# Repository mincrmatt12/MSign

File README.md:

# MSign

Code + designs for an LED sign display board powered by an STM32 and ESP8266. Make sure you clone the submodules.

## Organization

- `board`: schematics and PCB layout
- `stm`: STM32 firmware (drives the display)
- `stmboot`: STM32 bootloader
- `esp`: ESP8266 firmware (grabs information from the internet)
- `espweb`: ESP8266 web-based configuration page source
- `cfgserver`: Server for shipping unattended config and software updates (without using the webui)
- `bmap`: Tools for generating graphics resources
- `caplog`: Tools for debugging
- `vendor`: Various dependencies in source form (everything not listed below)
- `sim`: Stubs/shims for running the `esp` and `stm` codebases under linux.

## Dependencies

- A recent `arm-none-eabi-gcc` installation (suitably modern to deal with C++20; GCC 14 is what's tested)
- A `xtensa-lx106-elf-gcc` that can deal with C++20; preferably version 13.2.0 (which was available at one point in debian)
  - A suitable newlib/libstdc++ archive is available in `Dockerfile.build`
- Python 3 and the packages in `requirements.txt`
  - If you aren't building the `espweb` directory you do not require the `cryptography` package listed
- OpenOCD (for flashing)
  - If you have PlatformIO installed we use its OpenOCD by default, so you may not need to install it system-wide.
- CMake (version 3.13 or later is recommended)
- `quilt`, to apply the patches in `vendor` for the ESP8266 SDK

and everything checked out in the `vendor` directory. The ESP8266 SDK also usually requests you have python (specifically _system_ python, whatever runs from `python`) installed with it's requirements (`vendor/ESP8266_RTOS_SDK/requirements.txt`)

A Docker file with these is provided as `Dockerfile.build`.

For building the `espweb` you also need:

- yarn
- node 

A Docker file with _these_ is also provided as `Dockerfile.webbuild`

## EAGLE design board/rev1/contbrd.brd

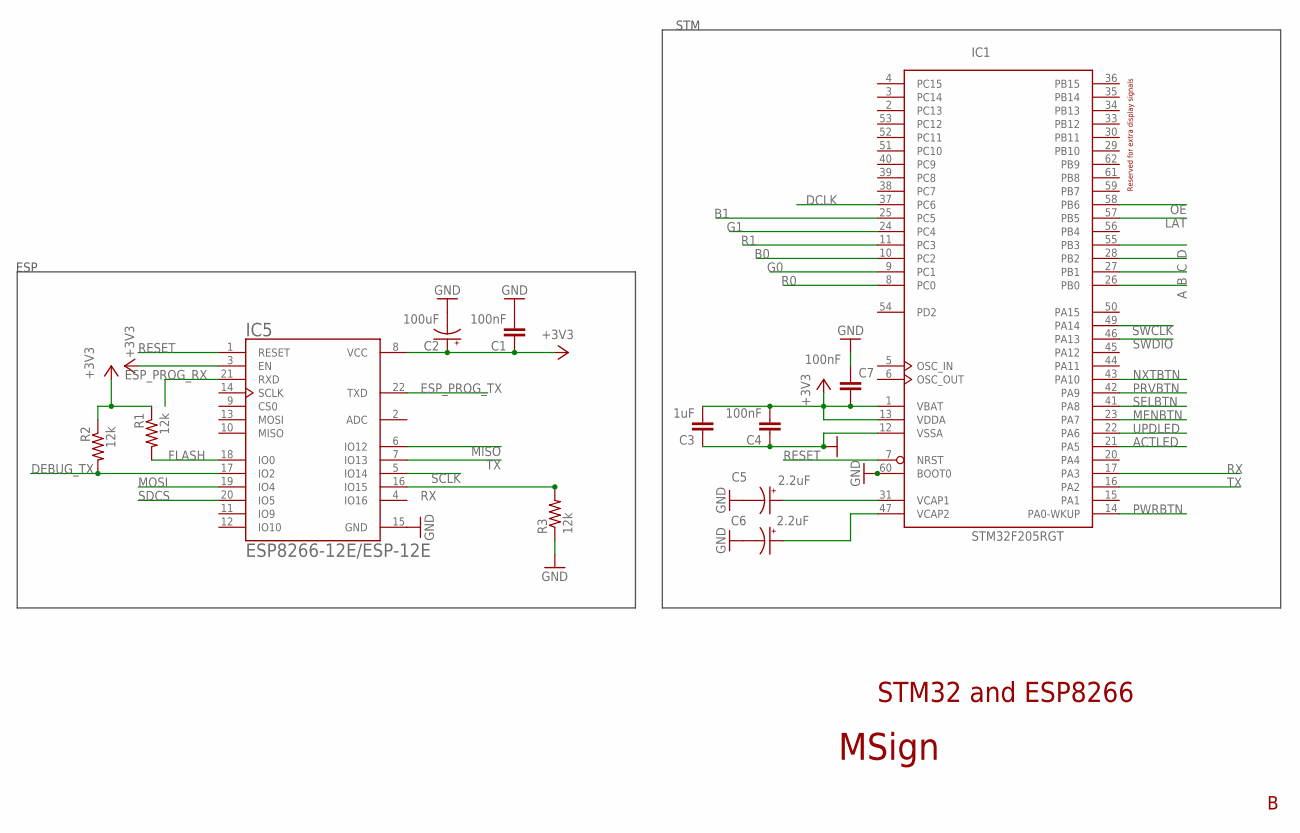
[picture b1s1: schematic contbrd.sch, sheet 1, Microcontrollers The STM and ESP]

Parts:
C1, C4, C7: 100nF; C025-025X050
C2: 100uF; E2,5-6
C3: 1uF; C050-024X044
C5, C6: 2.2uF; E1,8-4
IC1: STM32F205RGT; LQFP64
IC5: ESP8266-12E/ESP-12E; XCVR_ESP8266-12E/ESP-12E
R1, R2, R3: 12k; 0204/7

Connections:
+3V3: C1.1, C2.+, C3.2, C4.2, C7.2, IC1.1 (VBAT), IC1.13 (VDDA), IC5.3 (EN), IC5.8 (VCC), R1.1, R2.1; also elsewhere on the board
A: IC1.26 (PB0); also elsewhere on the board
ACTLED: IC1.21 (PA5); also elsewhere on the board
B: IC1.27 (PB1); also elsewhere on the board
B0: IC1.10 (PC2); also elsewhere on the board
B1: IC1.25 (PC5); also elsewhere on the board
C: IC1.28 (PB2); also elsewhere on the board
D: IC1.55 (PB3); also elsewhere on the board
DCLK: IC1.37 (PC6); also elsewhere on the board
DEBUG_TX: IC5.17 (IO2), R2.2; also elsewhere on the board
ESP_PROG_RX: IC5.21 (RXD); also elsewhere on the board
ESP_PROG_TX: IC5.22 (TXD); also elsewhere on the board
FLASH: IC5.18 (IO0), R1.2; also elsewhere on the board
G0: IC1.9 (PC1); also elsewhere on the board
G1: IC1.24 (PC4); also elsewhere on the board
GND: C1.2, C2.-, C3.1, C4.1, C5.-, C6.-, C7.1, IC1.12 (VSSA), IC1.60 (BOOT0), IC5.15 (GND), R3.1; also elsewhere on the board
LAT: IC1.57 (PB5); also elsewhere on the board
MENBTN: IC1.23 (PA7); also elsewhere on the board
MISO: IC5.6 (IO12); also elsewhere on the board
MOSI: IC5.19 (IO4); also elsewhere on the board
unnamed: C5.+, IC1.31 (VCAP1)
unnamed: C6.+, IC1.47 (VCAP2)
NXTBTN: IC1.43 (PA10); also elsewhere on the board
OE: IC1.58 (PB6); also elsewhere on the board
PRVBTN: IC1.42 (PA9); also elsewhere on the board
PWRBTN: IC1.14 (PA0-WKUP); also elsewhere on the board
R0: IC1.8 (PC0); also elsewhere on the board
R1: IC1.11 (PC3); also elsewhere on the board
RESET: IC1.7 (NRST), IC5.1 (RESET); also elsewhere on the board
RX: IC1.17 (PA3), IC5.16 (IO15), R3.2
SCLK: IC5.5 (IO14); also elsewhere on the board
SDCS: IC5.20 (IO5); also elsewhere on the board
SELBTN: IC1.41 (PA8); also elsewhere on the board
SWCLK: IC1.49 (PA14); also elsewhere on the board
SWDIO: IC1.46 (PA13); also elsewhere on the board
TX: IC1.16 (PA2), IC5.7 (IO13)
UPDLED: IC1.22 (PA6); also elsewhere on the board

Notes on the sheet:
ESP
STM
MSign
STM32 and ESP8266
Reserved for extra display signals

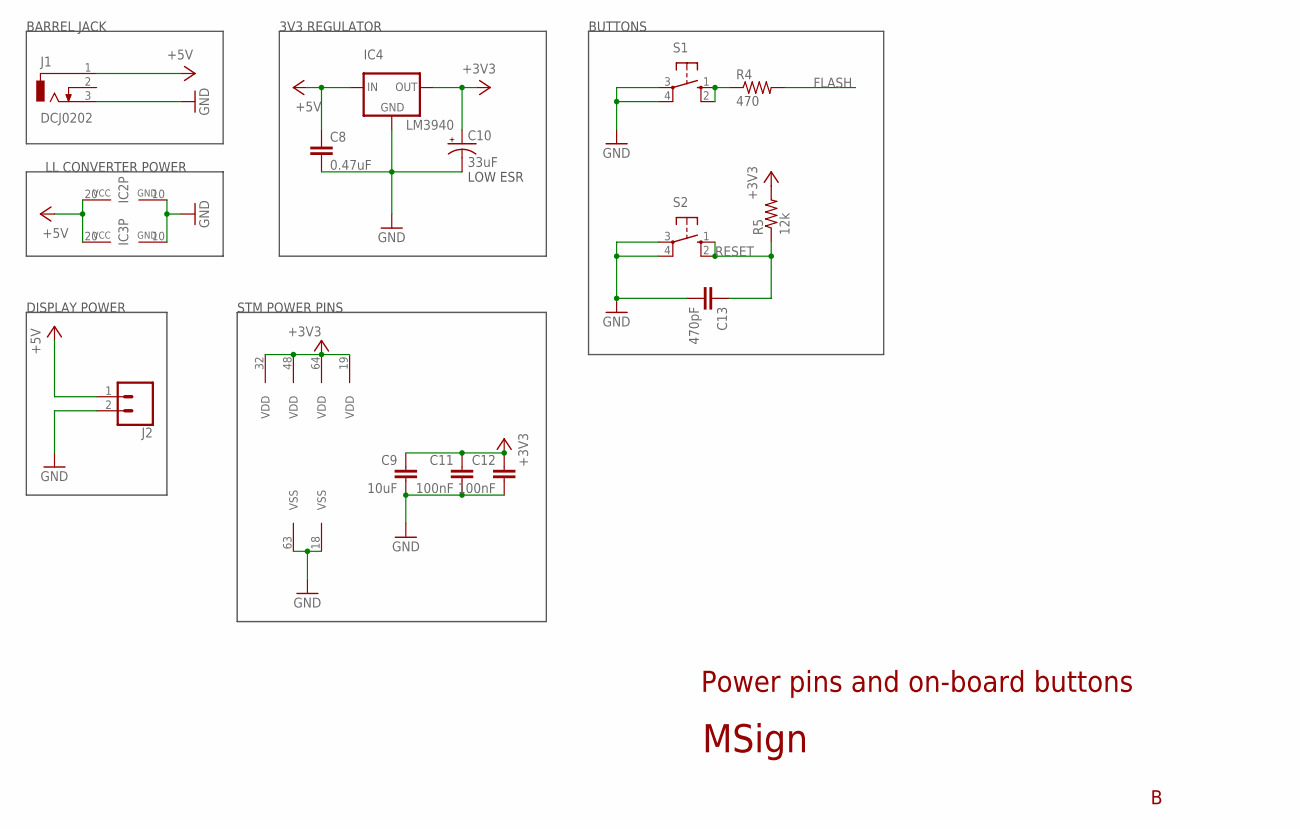
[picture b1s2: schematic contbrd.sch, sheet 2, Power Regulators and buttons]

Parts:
C8: 0.47uF; C050-024X044
C9: 10uF; C025-025X050
C10: 33uF; E2-5
C11, C12: 100nF; C025-025X050
C13: 470pF; C025-025X050
IC1: STM32F205RGT; LQFP64
IC2, IC3: 74HCT244DW; SO20W
IC4: LM3940; TO220
J1: DCJ0202
J2: CONN_025MM; SCREWTERMINAL-5MM-2
R4: 470; 0204/7
R5: 12k; 0204/7
S1, S2: 10-XX; B3F-10XX

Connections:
+3V3: C9.1, C10.+, C11.1, C12.1, IC1.19 (VDD), IC1.32 (VDD), IC1.48 (VDD), IC1.64 (VDD), IC4.3 (OUT), R5.2; also elsewhere on the board
+5V: C8.1, IC2.20 (VCC), IC3.20 (VCC), IC4.1 (IN), J1.1, J2.1
FLASH: R4.2; also elsewhere on the board
GND: C8.2, C9.2, C10.-, C11.2, C12.2, C13.2, IC1.18 (VSS), IC1.63 (VSS), IC2.10 (GND), IC3.10 (GND), IC4.2 (GND), J1.3, J2.2, S1.3, S1.4 (P1), S2.3, S2.4 (P1); also elsewhere on the board
unnamed: R4.1, S1.1 (S), S1.2 (S1)
RESET: C13.1, R5.1, S2.1 (S), S2.2 (S1); also elsewhere on the board

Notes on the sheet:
DISPLAY POWER
BARREL JACK
LOW ESR
STM POWER PINS
3V3 REGULATOR
BUTTONS
LL CONVERTER POWER
MSign
Power pins and on-board buttons

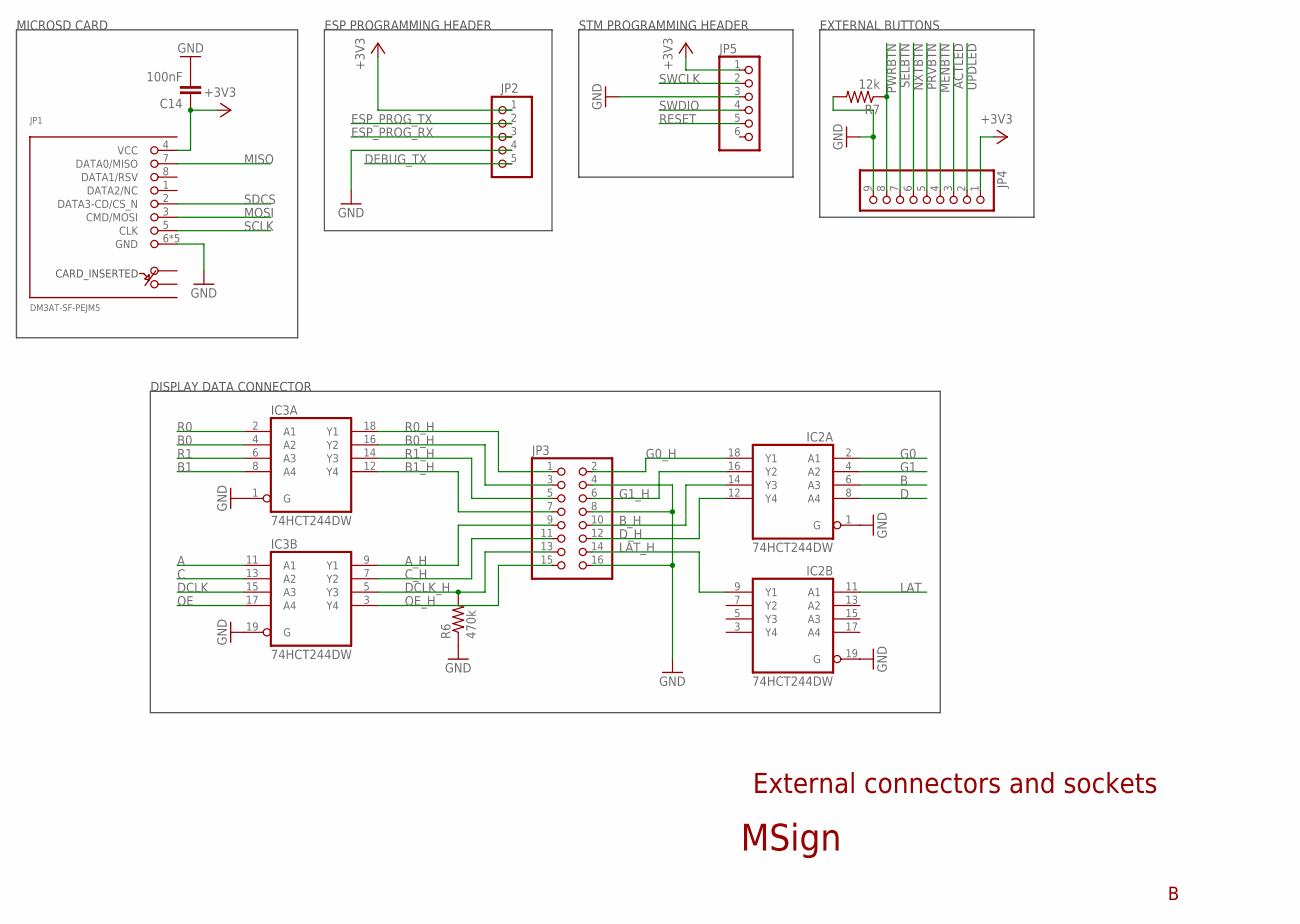
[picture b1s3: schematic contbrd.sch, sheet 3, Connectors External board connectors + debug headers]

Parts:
C14: 100nF; C025-025X050
IC2, IC3: 74HCT244DW; SO20W
JP1: DM3AT-SF-PEJM5
JP2: PINHD-1X5; 1X05
JP3: PINHD-2X8; 2X08
JP4: PINHD-1X9; 1X09
JP5: PINHD-1X6; 1X06
R6: 470k; 0204/7
R7: 12k; 0204/7

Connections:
+3V3: C14.1, JP1.4 (VCC), JP2.1, JP4.1, JP5.1; also elsewhere on the board
A: IC3.11 (A1); also elsewhere on the board
ACTLED: JP4.3; also elsewhere on the board
A_H: IC3.9 (Y1), JP3.9
B: IC2.6 (A3); also elsewhere on the board
B0: IC3.4 (A2); also elsewhere on the board
B0_H: IC3.16 (Y2), JP3.3
B1: IC3.8 (A4); also elsewhere on the board
B1_H: IC3.12 (Y4), JP3.7
B_H: IC2.14 (Y3), JP3.10
C: IC3.13 (A2); also elsewhere on the board
C_H: IC3.7 (Y2), JP3.11
D: IC2.8 (A4); also elsewhere on the board
DCLK: IC3.15 (A3); also elsewhere on the board
DCLK_H: IC3.5 (Y3), JP3.13, R6.2
DEBUG_TX: JP2.5; also elsewhere on the board
D_H: IC2.12 (Y4), JP3.12
ESP_PROG_RX: JP2.3; also elsewhere on the board
ESP_PROG_TX: JP2.2; also elsewhere on the board
G0: IC2.2 (A1); also elsewhere on the board
G0_H: IC2.18 (Y1), JP3.2
G1: IC2.4 (A2); also elsewhere on the board
G1_H: IC2.16 (Y2), JP3.6
GND: C14.2, IC2.1 (G), IC2.19 (G), IC3.1 (G), IC3.19 (G), JP1.6 (GND), JP1.MOUNT0 (GND), JP1.MOUNT1 (GND), JP1.MOUNT2 (GND), JP1.MOUNT3 (GND), JP2.4, JP3.4, JP3.8, JP3.16, JP4.9, JP5.3, R6.1, R7.2; also elsewhere on the board
LAT: IC2.11 (A1); also elsewhere on the board
LAT_H: IC2.9 (Y1), JP3.14
MENBTN: JP4.4; also elsewhere on the board
MISO: JP1.7 (DATA0/MISO); also elsewhere on the board
MOSI: JP1.3 (CMD/MOSI); also elsewhere on the board
NXTBTN: JP4.6; also elsewhere on the board
OE: IC3.17 (A4); also elsewhere on the board
OE_H: IC3.3 (Y4), JP3.15
PRVBTN: JP4.5; also elsewhere on the board
PWRBTN: JP4.8, R7.1; also elsewhere on the board
R0: IC3.2 (A1); also elsewhere on the board
R0_H: IC3.18 (Y1), JP3.1
R1: IC3.6 (A3); also elsewhere on the board
R1_H: IC3.14 (Y3), JP3.5
RESET: JP5.5; also elsewhere on the board
SCLK: JP1.5 (CLK); also elsewhere on the board
SDCS: JP1.2 (DATA3-CD/CS_N); also elsewhere on the board
SELBTN: JP4.7; also elsewhere on the board
SWCLK: JP5.2; also elsewhere on the board
SWDIO: JP5.4; also elsewhere on the board
UPDLED: JP4.2; also elsewhere on the board

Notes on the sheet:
DISPLAY DATA CONNECTOR
MICROSD CARD
ESP PROGRAMMING HEADER
STM PROGRAMMING HEADER
MSign
External connectors and sockets
EXTERNAL BUTTONS

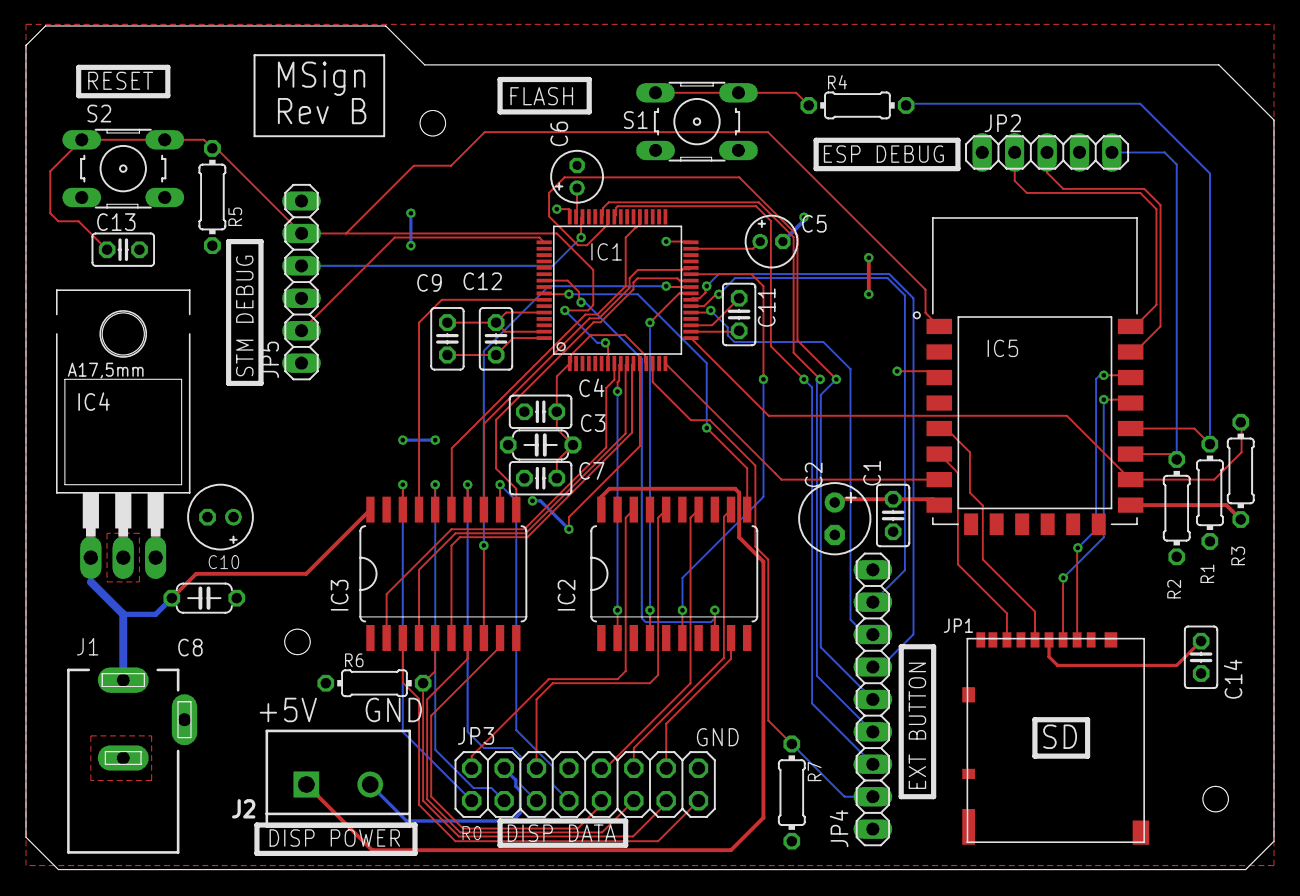
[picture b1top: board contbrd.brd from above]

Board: 2 copper layers, 97.8 x 66.1 mm, 35 parts (0 on the bottom side), 52 nets.

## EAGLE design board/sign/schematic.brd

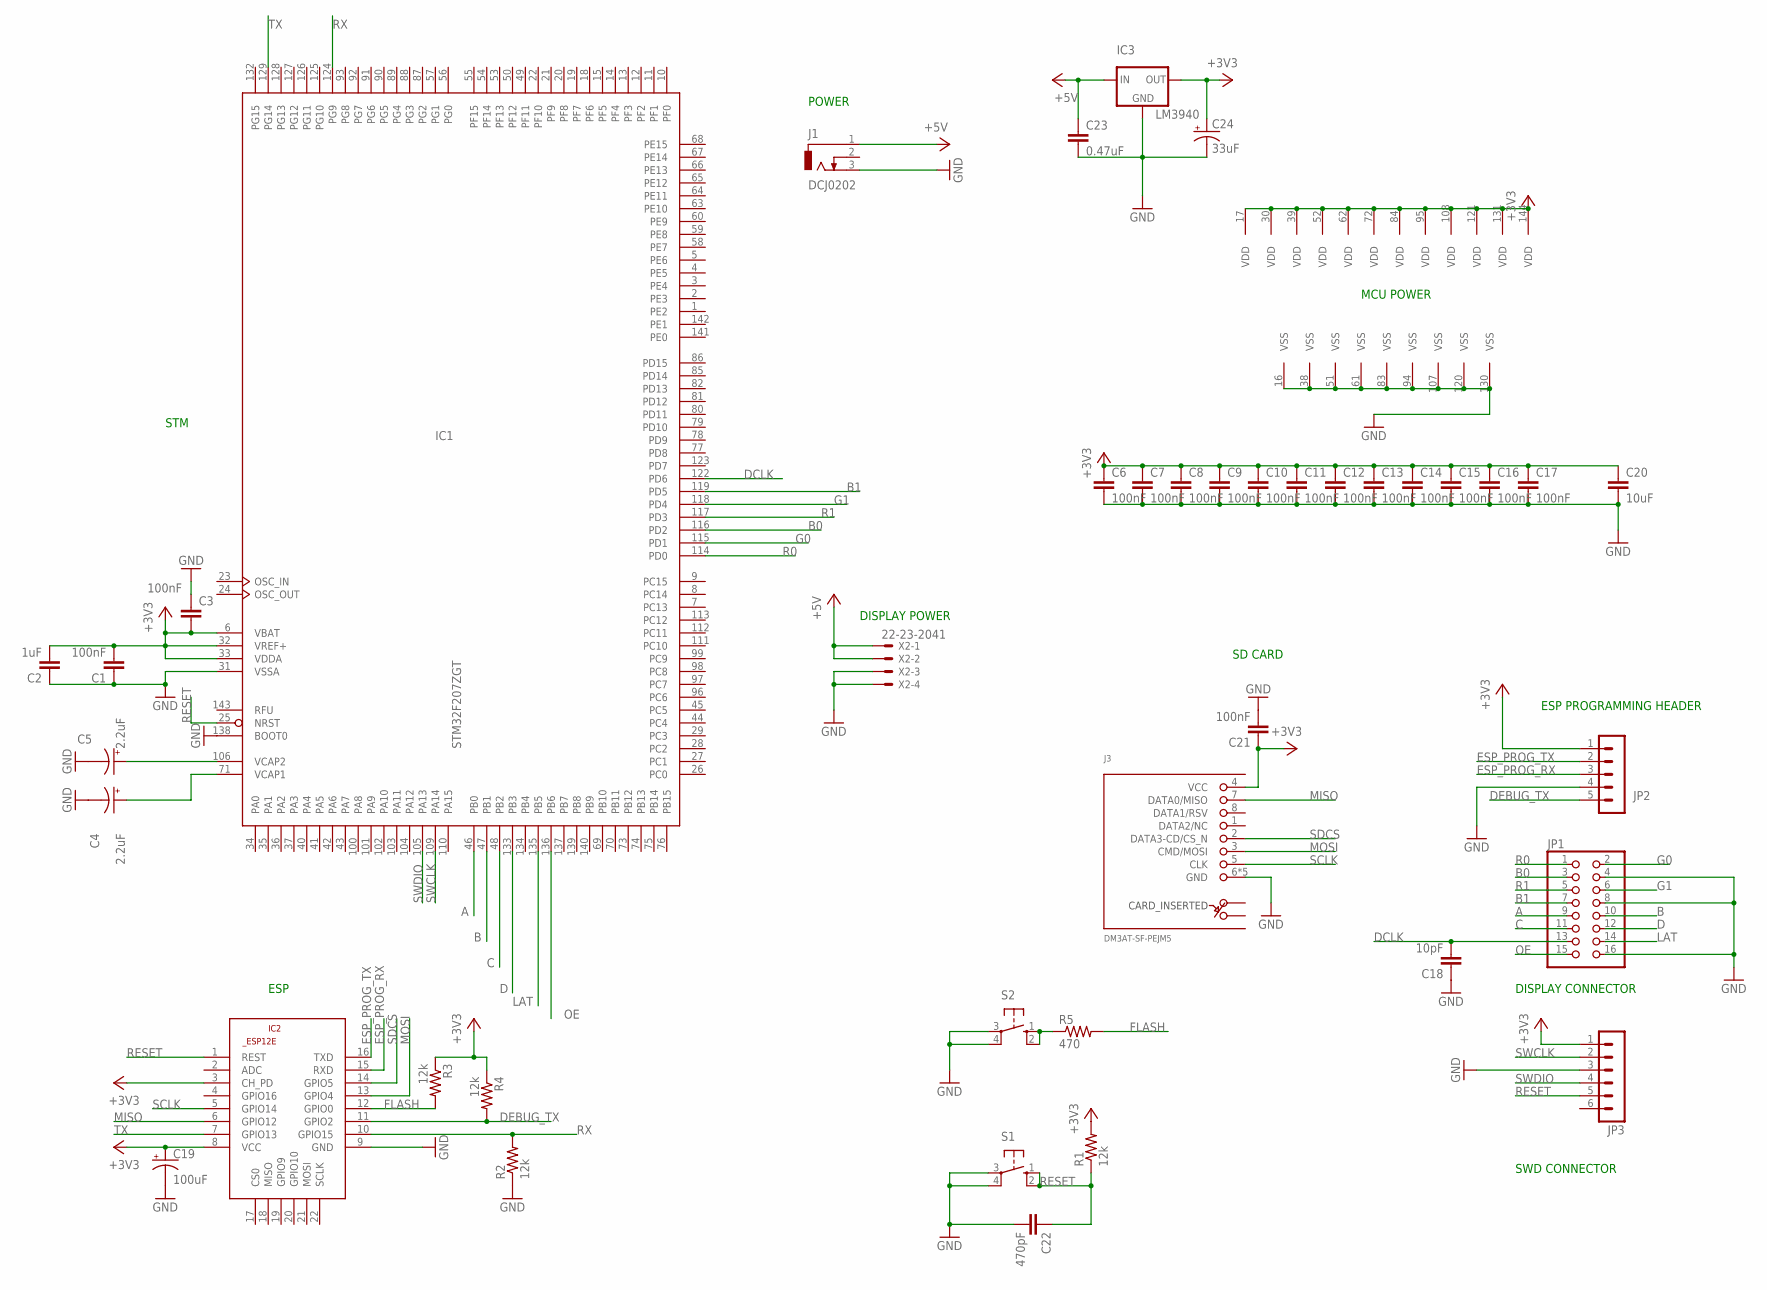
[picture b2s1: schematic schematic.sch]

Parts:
C1, C3, C6, C7, C8, C9, C10, C11, C12, C13, C14, C15, C16, C17, C21: 100nF; C025-025X050
C2: 1uF; C050-024X044
C4, C5: 2.2uF; E1,8-4
C18: 10pF; C050-024X044
C19: 100uF; E2,5-6
C20: 10uF; C025-025X050
C22: 470pF; C025-025X050
C23: 0.47uF; C050-024X044
C24: 33uF; E2-5
IC1: STM32F207ZGT; LQFP144
IC2: ESP8266-12EESP12E; ESP8266-ESP12E
IC3: LM3940; TO220
J1: DCJ0202
J3: DM3AT-SF-PEJM5
JP1: PINHD-2X8; 2X08
JP2: MA05-1
JP3: MA06-1
R1, R2, R3, R4: 12k; 0204/7
R5: 470; 0204/7
S1, S2: 10-XX; B3F-10XX
X2: 22-23-2041

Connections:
+3V3: C1.2, C2.2, C3.2, C6.1, C7.1, C8.1, C9.1, C10.1, C11.1, C12.1, C13.1, C14.1, C15.1, C16.1, C17.1, C19.+, C20.1, C21.1, C24.+, IC1.6 (VBAT), IC1.17 (VDD), IC1.30 (VDD), IC1.32 (VREF+), IC1.33 (VDDA), IC1.39 (VDD), IC1.52 (VDD), IC1.62 (VDD), IC1.72 (VDD), IC1.84 (VDD), IC1.95 (VDD), IC1.108 (VDD), IC1.121 (VDD), IC1.131 (VDD), IC1.144 (VDD), IC2.3 (CH_PD), IC2.8 (VCC), IC3.3 (OUT), J3.4 (VCC), JP2.1, JP3.1, R1.2, R3.1, R4.1
+5V: C23.1, IC3.1 (IN), J1.1, X2.1, X2.2
A: IC1.46 (PB0), JP1.9
B: IC1.47 (PB1), JP1.10
B0: IC1.116 (PD2), JP1.3
B1: IC1.119 (PD5), JP1.7
C: IC1.48 (PB2), JP1.11
D: IC1.133 (PB3), JP1.12
DCLK: C18.2, IC1.122 (PD6), JP1.13
DEBUG_TX: IC2.11 (GPIO2), JP2.5, R4.2
ESP_PROG_RX: IC2.15 (RXD), JP2.3
ESP_PROG_TX: IC2.16 (TXD), JP2.2
FLASH: IC2.12 (GPIO0), R3.2, R5.2
G0: IC1.115 (PD1), JP1.2
G1: IC1.118 (PD4), JP1.6
GND: C1.1, C2.1, C3.1, C4.-, C5.-, C6.2, C7.2, C8.2, C9.2, C10.2, C11.2, C12.2, C13.2, C14.2, C15.2, C16.2, C17.2, C18.1, C19.-, C20.2, C21.2, C22.2, C23.2, C24.-, IC1.16 (VSS), IC1.31 (VSSA), IC1.38 (VSS), IC1.51 (VSS), IC1.61 (VSS), IC1.83 (VSS), IC1.94 (VSS), IC1.107 (VSS), IC1.120 (VSS), IC1.130 (VSS), IC1.138 (BOOT0), IC2.9 (GND), IC3.2 (GND), J1.3, J3.6 (GND), J3.MOUNT0 (GND), J3.MOUNT1 (GND), J3.MOUNT2 (GND), J3.MOUNT3 (GND), JP1.4, JP1.8, JP1.16, JP2.4, JP3.3, R2.1, S1.3, S1.4 (P1), S2.3, S2.4 (P1), X2.3, X2.4
LAT: IC1.135 (PB5), JP1.14
MISO: IC2.6 (GPIO12), J3.7 (DATA0/MISO)
MOSI: IC2.13 (GPIO4), J3.3 (CMD/MOSI)
unnamed: R5.1, S2.1 (S), S2.2 (S1)
unnamed: C5.+, IC1.106 (VCAP2)
unnamed: C4.+, IC1.71 (VCAP1)
OE: IC1.136 (PB6), JP1.15
R0: IC1.114 (PD0), JP1.1
R1: IC1.117 (PD3), JP1.5
RESET: C22.1, IC1.25 (NRST), IC2.1 (REST), JP3.5, R1.1, S1.1 (S), S1.2 (S1)
RX: IC1.124 (PG9), IC2.10 (GPIO15), R2.2
SCLK: IC2.5 (GPIO14), J3.5 (CLK)
SDCS: IC2.14 (GPIO5), J3.2 (DATA3-CD/CS_N)
SWCLK: IC1.109 (PA14), JP3.2
SWDIO: IC1.105 (PA13), JP3.4
TX: IC1.129 (PG14), IC2.7 (GPIO13)

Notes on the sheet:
MCU POWER
DISPLAY POWER
POWER
SD CARD
ESP
STM
DISPLAY CONNECTOR
ESP PROGRAMMING HEADER
SWD CONNECTOR

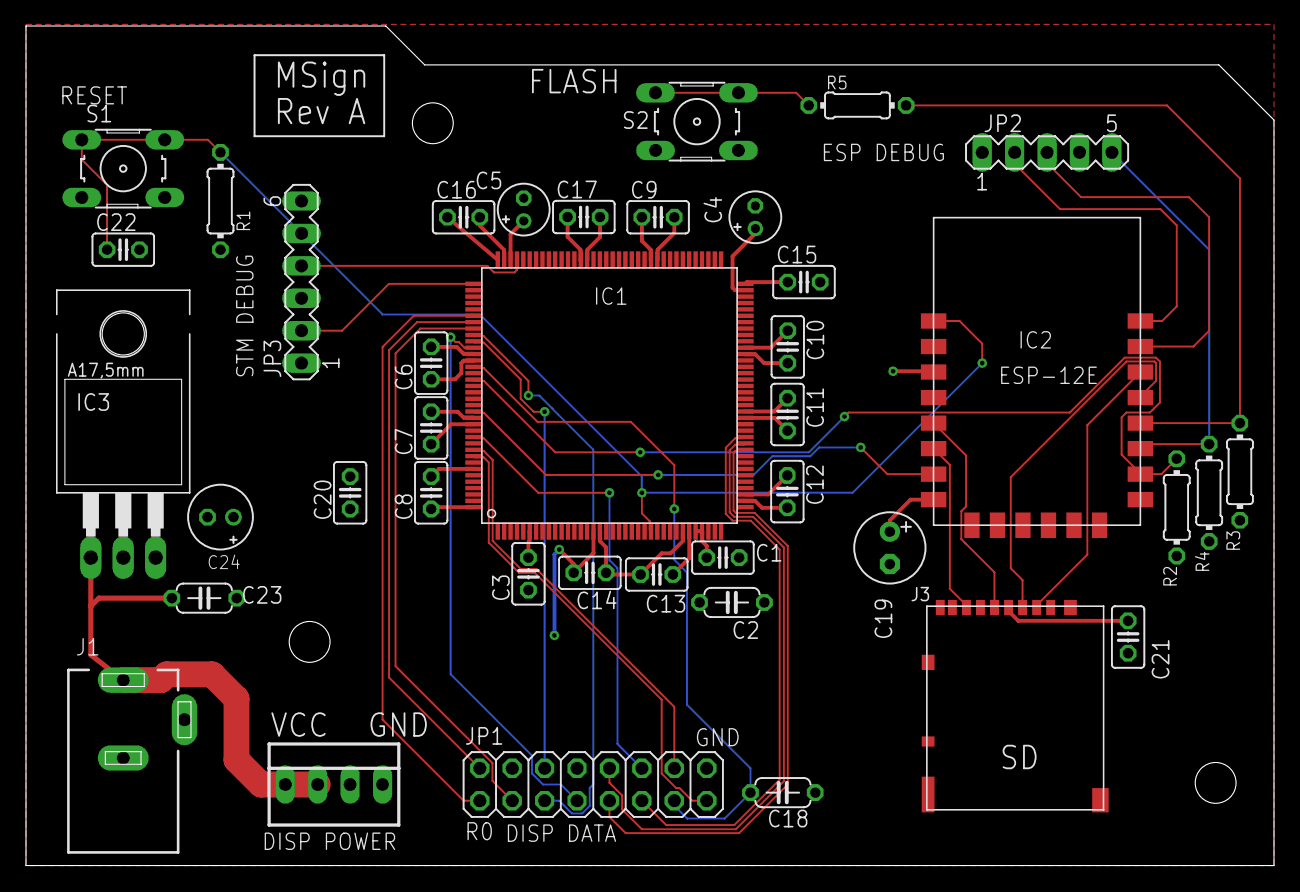
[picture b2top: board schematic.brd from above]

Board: 2 copper layers, 97.8 x 65.8 mm, 40 parts (0 on the bottom side), 32 nets.

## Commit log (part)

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2023-12-26 Add script to unpack a json dump with slotlib prettyprinting
2023-12-26 Sync octoprint on 409 case because update_slot() was going the nocopy route
2023-12-27 Add more outline text overloads
2023-12-27 Remove geocoding
2023-12-27 Fix template deduction on GCC 12
2023-12-27 Reopen file
2023-12-27 More sd error checking pt the third
    this time for writes not reads!
2023-12-27 Hide filename when no print job is loaded
2023-12-28 Fix octoprint grabber completion
    (from 0-100, not 0-1)
2023-12-28 Add printer icon animation
2023-12-28 Add new octoprint options to webui
2023-12-28 Scale bitmaps to dim - 1 instead of dim
    we want the pixels to occupy coordinates from [0, dim), so we
    need to multiply the 0.0-1.0 coords by dim - 1, not dim
2023-12-30 Adjust dupm queue timeout to 0 for requests from serial
    This prevents a deadlock of the form:
    - dupm queue fills
    - dupm waits for packet
    - serial gets a DATA_TEMP message
    - serial waits for 5 seconds for empty space in dupm
    - dupm wait timeout expires
2023-12-31 Implement analog stick
2023-12-31 Use up as virtual previous, not down
2023-12-31 Swap ADC pins with TAB/SEL buttons
    their original pins are not adc inputs. rev2 board will fix this if
    I ever manufacture it
2023-12-31 Ignore kicad lock files in board/
2023-12-31 Add joystick interaction to octoprint screen
    also speed up rendering hopefully with faster rounding
2023-12-31 Fix duplicated scroll table entry
2024-01-01 Add more fs validation in the octoprint bitmap handler
2024-01-01 Ensure restarting HTTP reconnects to try to avoid octoprint kicking us for being slow
2024-01-02 Use midnight as end of day for parcel est. delivery
2024-01-04 Document required fields
2024-01-04 Quantize times to <5minutes where applicable.
2024-01-05 Limit minutely data
2024-01-06 Add serial::interface.update_slot_at_inline
2024-01-06 Fix infinite loop in precip graph draw
2024-01-06 Resolve all interrupt handlers in log to names
2024-01-06 Ensure stm_crash target gets -O2 at least
2024-01-06 Fix missing sync after appending to summary buffer
    also wrong length calc
2024-01-06 Be less conservative in deeming precipitation "unlikely"
2024-01-06 Send grab task high watermark in metrics reports
2024-01-07 Adjust wording for "tomorrow night" when referring to next morning
2024-01-07 Fix rounding issues in bheap
    Problems resulting from the previous fix (now instead of bheap
    corruption, we had bheap infinite loops!)
2024-01-07 Remove erroneous public: in bheap method
    (was added for testing, forgot to remove)
2024-01-07 Add vendor/ to rgignore
2024-01-08 Fix missing "and" in summarizer
2024-01-09 Adjust interaction speeds in weather graph
2024-01-10 Adjust windy icon threshold
2024-01-10 Fix weathersummarizer fusing of unbounded minutely blocks
2024-01-12 Fix cfgserver typos
2024-01-12 Bump cfgserver to 0.1.5
2024-01-25 Ensure cache dir exists in yarn container
2024-02-03 Fix wtest argc check
2024-02-09 Ensure fused data does not limit precision in summaries
2024-02-13 Fix broken check for previous amt in summarizer
2024-02-13 Remove max_hourly_precision in favour of per-timespec precision
2024-03-11 Begin five-day forecast view
2024-03-11 Add five-day forecast view
2024-03-11 Fix arrows in fiveday view
2024-03-18 Add ESP8266 panic/crashlog saving
    After a fatal error, we write the crashlog contents (or at least
    the backtrace; the other PANIC() messages aren't captured at the moment)
    into RAM, then on the next boot we write that message to the SD card.
2024-03-18 Ensure no null bytes wind up in crash log files
2024-03-23 Ensure STM does not freeze after ESP crash during sleep
2024-04-19 Fix detection of likely/unlikely precipitation
2024-04-23 Use a heap-allocated larger file send buffer where possible
2024-06-07 Put minimum bound on precipitation probability when the icon is set
    This avoids a lot of the "rain starting in <5 minutes" summaries that
    go on perpetually despite the server-side icon assignments making
    physical sense.
2024-06-08 Halfhearted attempt to deal with hour 0 offset in minutes
    really should be plumbed through as_minutes()
2024-06-15 Add translate_messages to espweb
2024-06-16 Fix should_ignore_hourly_summary
2024-06-18 Revert broken fix in weathersummarizer
2024-06-24 Show parcel status when only icon is available
2024-06-24 Fix condition in parcels
2024-06-24 Fix alignment
2024-06-28 Remove unused class icons
    (used to be in tdsb grabber, no longer used)
2024-06-29 Store snow depth instead of speed on daily precip
2024-06-29 Add raw_timestamp to espweb
2024-07-03 Refactor parcel status matching
2024-07-03 Fix buggy weather data fuse
    Still obviously not considering the actual hour offset but meh.
2024-07-08 Remove unused vera_8 font
2024-07-10 Limit range on hourly precipitation to preserve precision
2024-07-11 Fix parcel long scroll flicker
2024-07-13 update buttons kicad project files after kicad 8
    some extra fields get generated... who knows?
2024-07-13 Remove libc dependency from stmboot
    Also doesn't link against libgcc, which is technically wrong but the
    bootloader is not meant to use any of the things libgcc fills anyways.
2024-07-14 Remove stm dependency on newlib
    The entirety of the stm codebase right now only relied on:
    - mem{move,cpy,set}: trivial to reimplement (even without
    optimizations, just using -O3 on a naive implementation generates
    suitable unrolling)
    - strlen & strncpy: also trivial to implement
    - strftime & gmtime_r: replaced with c++ quasi-time.h implementation
2024-07-14 Fix stm build scripts always regenerating stm.bin
2024-07-15 Fix out-of-bounds write in dupm
2024-07-15 Update ESP toolchain
    ARM: 13.3 -> (unchanged)
    ESP: 8.4.0 -> 13.2 (built from 8.4.0 newlib, 13.2 esp32 libstdc++ and debian GCC)
    Debian: bookworm -> trixie
2024-07-15 Fix dockerfile to work from an unpatched SDK
2024-07-22 Allow wildcard dirtag matches in ttc
2024-08-09 Add degree symbol to tahoma_9 font
2024-08-09 Enhance descriptions of weather graphs
    also using the new ° symbol in the font
2024-09-01 Add entry to clangd to remove charset override
    clang doesn't seem to like `cp1252` as a charset
2024-09-01 Adjust gamma from 2.6 to 2.45
    as an experiment
2024-09-07 Minor tweak in locking around slots::TTC_INFO
2024-10-01 Adjust colors on weather for fog
2024-10-01 Fix bug with e-notation in json parser
2024-10-01 Check for memory alloc fail in bearssl_supplicant
2024-10-01 Move lwip clone from savannah.nongnu to the github mirror
2024-10-11 Set wifi free heap threshold to 10k
2024-10-22 Try to re-init wifi after disconnect fail
2024-10-28 Upgrade js dependencies to appease dependabot
2024-10-28 actually call esp_wifi_connect in the reset code
2024-10-30 Fix weather graph occasionally showing negative wind
2024-11-10 Add fix for memory leak in sdk code
    When reconnecting to a WPA2-Enterprise network, the system can decide
    to cache on a reconnection attempt, in which case the EAP sm is not
    cleaned up and roughly 7k is leaked (well, it's referenced by a global
    so will not accumulate over multiple attempts, but still) as a result.
    This adds a few hacks to ensure the SDK code is told about key
    negotiation succeeding regardless - this is complicated by the fact that
2024-11-11 Cleanup TypedBlock helpers and add array size()
    uses requires to conditionally include methods instead of static
    asserts, far cleaner
    also adds a size() to return the array size of a pointer specialization
2024-11-20 Fix snow icon
2024-11-20 Discard GTFS updates if they are empty
    (using old information)
2024-11-20 Add clangd file for stm common
    fixes autocomplete by assuming a boring normal c++20 setup
    for the files which are completely standalone
2024-11-26 Avoid showing 0mm of snow if no accumulation, show rate instead
2024-11-27 Ensure enums with "negative" values get parsed by slotlib
2024-12-10 Add bitmask_of to slots.h
    and support in slotlib - used to mark bitmasks without using enum names
    (works better for multiple fields with same bitmask, like in new sccfg
    status reports)
2025-01-14 Set confgen to parse as c++20
2025-01-14 Fix incomplete refactor on sccfg
2025-01-18 Replace line_impl_low/high with a template
    (and also remove the redundant dx < 0/dy < 0 checks as we
    already swap the points natively)
2025-01-18 Add tailed block support to slotlib
    (bheap supports fixed-length header + dynamic trailer;
    only fixed types in slotlib atm)
2025-03-03 Unify draw::line low/high into a template
    also remove the redundant dx < 0 checks on the impl side
2025-03-03 Fix updates while sleeping
    (exits sleep for update)
2025-03-04 Avoid inlining fixed_t in octoprintbitmap
    (it's very large and would do better icached)
2025-03-05 Treat operational=false as disconnected in octoprint
2025-04-29 Avoid wind summaries with underwhelming wind
2025-04-29 Fix CI build due to newer xtensa gcc
    Pins ESP toolchian at gcc 13.2
    I do not feel like recreating the UNHOLY FUSION that is the
    newlib-libstdc++-xtensa-lx106-elf-13.2.0.tar.xz archive at the moment.
    (more importantly, it's based on the official ESP32 sources and they
    never released a 13.3 build).
2025-09-20 Upgrade toolchains in build
    ARM GCC: 13.2 -> debian build (14)
2025-10-14 Update ESP sdk
    fixes submodule urls in git, among other things
2025-10-18 Relax restrictions around ranged timespecs in summarizer
    improves situations like
    .##......... ##
    where you have a long uncertain tail and then a short gap, and
    then more precip; the summarizer instead takes center() in all cases
    which sounds dumb because it'll be measuring as if
    .####### ##
2025-10-23 Print finished text in green for octoprint
    also test change to Jenkins for included regions
2025-11-04 Fix three.js url
    yes i know esm is the right way to go nowadays; this code is ancient tho
2025-11-11 Add first chunk of rev2 PCB
    - power stage tentatively done
    - probably going to switch from sic951->sic451 with external
    inductor as it's far easier to get a hold of
    - still need to play with the eval boards for the sic951 which I
    have (i'd prefer to have the 451 but it's not in stock and i'm not
    paying for mouser shipping)
2025-11-11 remove sic951 --> start doing sic451
2025-11-11 Continue board work
    - move to rp2040, separate stm32g071 to do usb-c + aux ctrl IO
    - still cheaper lol with the cost of stm32s
    - more power reg stuff
2025-12-04 Bump @babel/runtime from 7.21.0 to 7.28.4 in /espweb
    Bumps [@babel/runtime](https://github.com/babel/babel/tree/HEAD/packages/babel-runtime) from 7.21.0 to 7.28.4.
    - [Release notes](https://github.com/babel/babel/releases)
    - [Changelog](https://github.com/babel/babel/blob/main/CHANGELOG.md)
    - [Commits](https://github.com/babel/babel/commits/v7.28.4/packages/babel-runtime)
    ---
    updated-dependencies:
2025-12-14 Continue board, assign caps/res, adjust for JLC availability
2025-12-15 Really finish rev2 board schematic
    - fix some more footprints
    - move to real SD card holder, for example
    - repair part numbers
    - add LCSC part refs to everything
    - add even more caps to the 3.3V reg output
    - really should use an LDO but meh it should be fine
2025-12-16 Add utf8 mode to jdump
2025-12-21 Abort webui cfg update if grab task is busy
    init can take a while, so this naturally ratelimits POST /config.json
2025-12-23 Show weather graph label for less time
2025-12-28 Layout more component blocks
    - regulators
    - mcus
    Still need to do the decoders + overall packing
2025-12-29 Fix cfgserver mimetype in metrics
2025-12-30 Use only one worker in cfgserver
    i forgot how crappy the metrics impl was lol
    should really make this use redis or something
2026-01-13 Steal patch from AUR to fix menuconfig
2026-01-22 Modernify readme requirements + bump copyright
2026-02-24 Bump lodash-es from 4.17.21 to 4.17.23 in /espweb
    Bumps lodash-es from 4.17.21 to 4.17.23.
    ---
    updated-dependencies:
    - dependency-name: lodash-es
    dependency-version: 4.17.23
    dependency-type: direct:production
2026-04-23 Add .history to gitignore (kicad 10)
2026-04-26 Add extra parameter changer to parcels page
2026-04-29 Track shipped time for progress bar in parcels

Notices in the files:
parts and their libraries:
SparkFun-Connectors: Licensing: Creative Commons ShareAlike 4.0 International - https://creativecommons.org/licenses/by-sa/4.0
